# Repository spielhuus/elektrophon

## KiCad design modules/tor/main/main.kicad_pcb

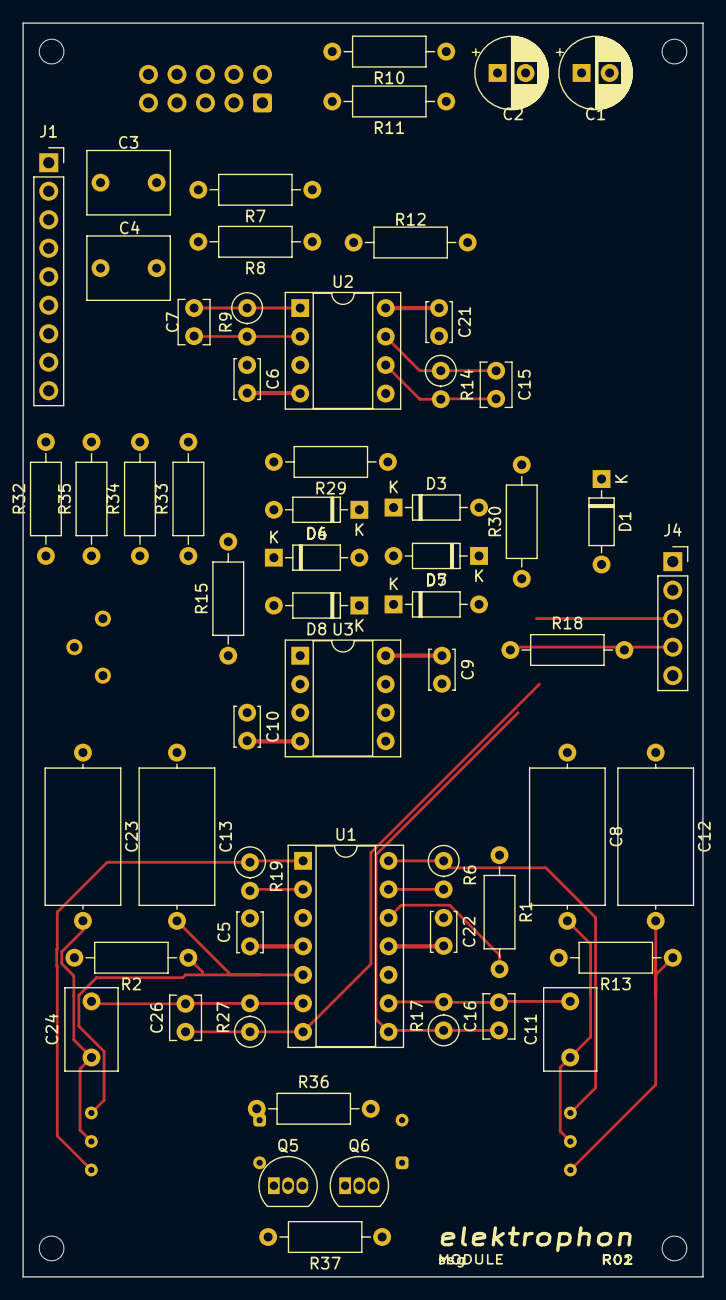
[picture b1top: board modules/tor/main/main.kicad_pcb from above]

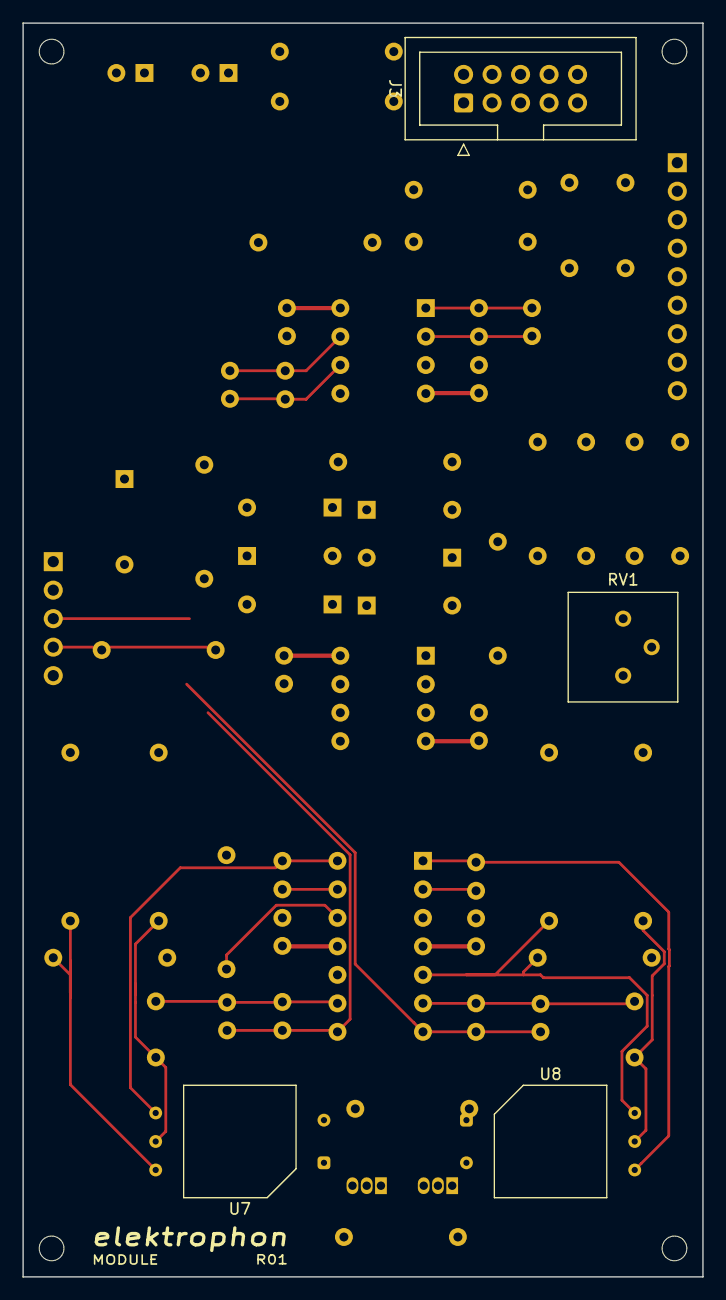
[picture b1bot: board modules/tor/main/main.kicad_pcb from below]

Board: 2 copper layers, 60.6 x 111.8 mm, 66 parts (4 on the bottom side), 44 nets.

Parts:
C1, C2: 22u; CP_Radial_D6.3mm_P2.50mm
C3, C4: 1u (NP); C_Rect_L7.2mm_W5.5mm_P5.00mm_FKS2_FKP2_MKS2_MKP2
C5, C6, C9, C10, C21, C22: 0.1u; C_Disc_D3.4mm_W2.1mm_P2.50mm
C7, C15, C16, C26: 47p; C_Disc_D3.8mm_W2.6mm_P2.50mm
C8, C23: 220p; C_Axial_L12.0mm_D6.5mm_P15.00mm_Horizontal
C11, C24: 4700p; C_Rect_L7.2mm_W4.5mm_P5.00mm_FKS2_FKP2_MKS2_MKP2
C12, C13: 1000p; C_Axial_L12.0mm_D6.5mm_P15.00mm_Horizontal
D1, D3, D4, D5, D6, D7, D8: 1N4148; D_DO-35_SOD27_P7.62mm_Horizontal
J1: Conn_01x09_Female; PinSocket_1x09_P2.54mm_Vertical
J3: IDC Header; IDC-Header_2x05_P2.54mm_Vertical
J4: Conn_01x05_Female; PinSocket_1x05_P2.54mm_Vertical
Q5: BC557; TO-92_Inline
Q6: BC547; TO-92_Inline
R1, R7, R8, R12, R15, R18, R30: 100k; R_Axial_DIN0207_L6.3mm_D2.5mm_P10.16mm_Horizontal
R2, R13: 4.7M; R_Axial_DIN0207_L6.3mm_D2.5mm_P10.16mm_Horizontal
R6, R19: 15k; R_Axial_DIN0207_L6.3mm_D2.5mm_P2.54mm_Vertical
R9, R14, R17, R27: 100k; R_Axial_DIN0207_L6.3mm_D2.5mm_P2.54mm_Vertical
R10, R11: 10; R_Axial_DIN0207_L6.3mm_D2.5mm_P10.16mm_Horizontal
R29: 10k; R_Axial_DIN0207_L6.3mm_D2.5mm_P10.16mm_Horizontal
R32, R33, R34, R35: 110k; R_Axial_DIN0207_L6.3mm_D2.5mm_P10.16mm_Horizontal
R36: 1.5k; R_Axial_DIN0207_L6.3mm_D2.5mm_P10.16mm_Horizontal
R37: 1Meg; R_Axial_DIN0207_L6.3mm_D2.5mm_P10.16mm_Horizontal
REF1, REF2, REF3, REF4: MountingHole_2.2mm_M2
RV1: 1k; Potentiometer_Bourns_3386P_Vertical
U1: TL074; DIP-14_W7.62mm_Socket
U2, U3: TL072; DIP-8_W7.62mm_Socket
U7, U8: VTL5Cx2; PerkinElmer_VTL5Cx2

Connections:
+5V: J3.9, J3.10
+15V: C1.1, C5.1, C9.1, C21.1, J1.2, R10.1, R37.1, U1.4, U2.8, U3.8, U7.2
-15V: C2.2, C6.2, C10.2, C22.2, Q5.1, R11.1, U1.11, U2.4, U3.4
/V1a: R6.1, U1.14, U7.5
/V1b: C8.2, C11.1, U7.4
/V1c: C12.2, R13.1, U1.10, U7.3
/V2a: R19.1, U1.1, U8.5
/V2b: C23.2, C24.1, U8.4
/V2c: C13.2, R2.1, U1.5, U8.3
CLIP: D1.2, J4.1
CV: J1.8, R35.2
CV2: J1.9, R32.2
FREQ: J1.7, R34.2
GND: C1.2, C2.1, C5.2, C6.1, C8.1, C9.2, C10.1, C12.1, C13.1, C21.2, C22.1, C23.1, J1.1, J3.5, J3.6, J3.7, J3.8, Q6.3, R1.1, R2.2, R13.2, R18.1, R30.1, R36.2, U2.3, U2.5
IN_1: C3.2, J1.3
IN_2: C4.2, J1.4
unnamed: C3.1, R7.2
unnamed: C4.1, R8.2
unnamed: C7.1, R9.1, R12.2, U2.1
unnamed: C7.2, R7.1, R8.1, R9.2, U2.2
unnamed: C11.2, C16.2, R17.2, U1.9
unnamed: C15.1, R1.2, R14.1, U1.12, U2.7
unnamed: C15.2, R12.1, R14.2, R15.2, U2.6
unnamed: C24.2, C26.2, R27.2, U1.6
unnamed: D1.1, D3.1, D4.2, R29.2, U3.3, U3.7
unnamed: D3.2, D5.1
unnamed: D4.1, D6.2
unnamed: D5.2, D7.1
unnamed: D6.1, D8.2
unnamed: D7.2, D8.1, R29.1, R30.2, U3.6
unnamed: Q5.2, R32.1, R33.1, R34.1, R35.1, RV1.1, RV1.2
unnamed: Q5.3, Q6.2, R37.2
unnamed: Q6.1, U8.1
unnamed: R6.2, U1.13
unnamed: R15.1, U3.1, U3.2
unnamed: R19.2, U1.2
unnamed: R36.1, RV1.3
unnamed: U7.1, U8.2
OUT_A: C16.1, J4.4, R17.1, R18.2, U1.3, U1.8
OUT_B: C26.1, J4.3, R27.1, U1.7
RES: J4.2, U3.5
VN: J3.1, J3.2, R11.2
VP: J3.3, J3.4, R10.2
V_OCT: J1.6, R33.2

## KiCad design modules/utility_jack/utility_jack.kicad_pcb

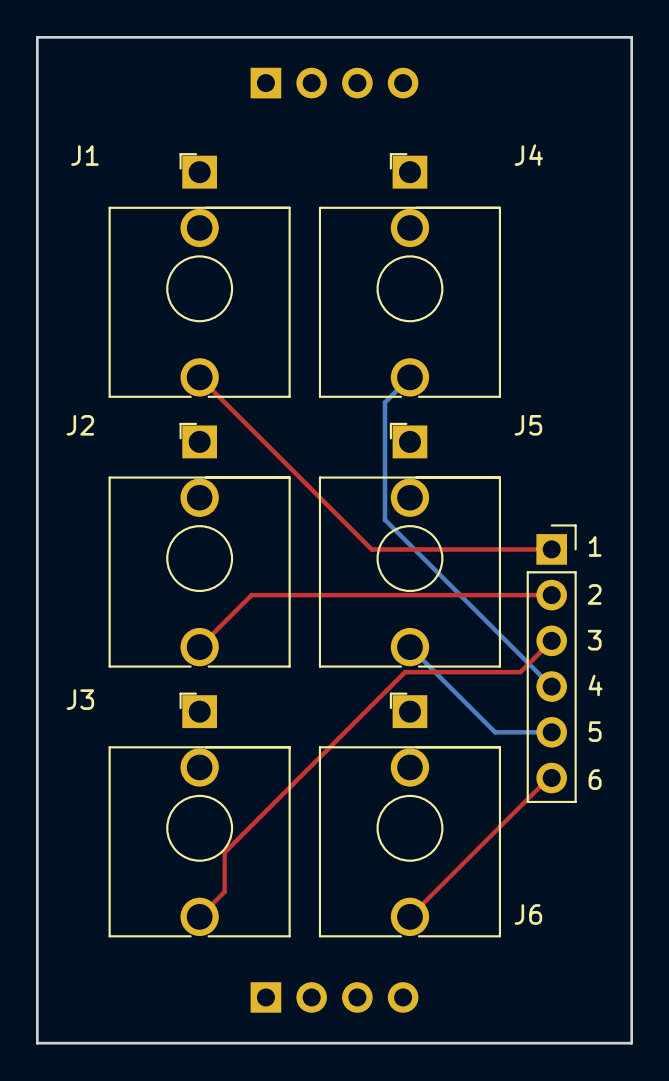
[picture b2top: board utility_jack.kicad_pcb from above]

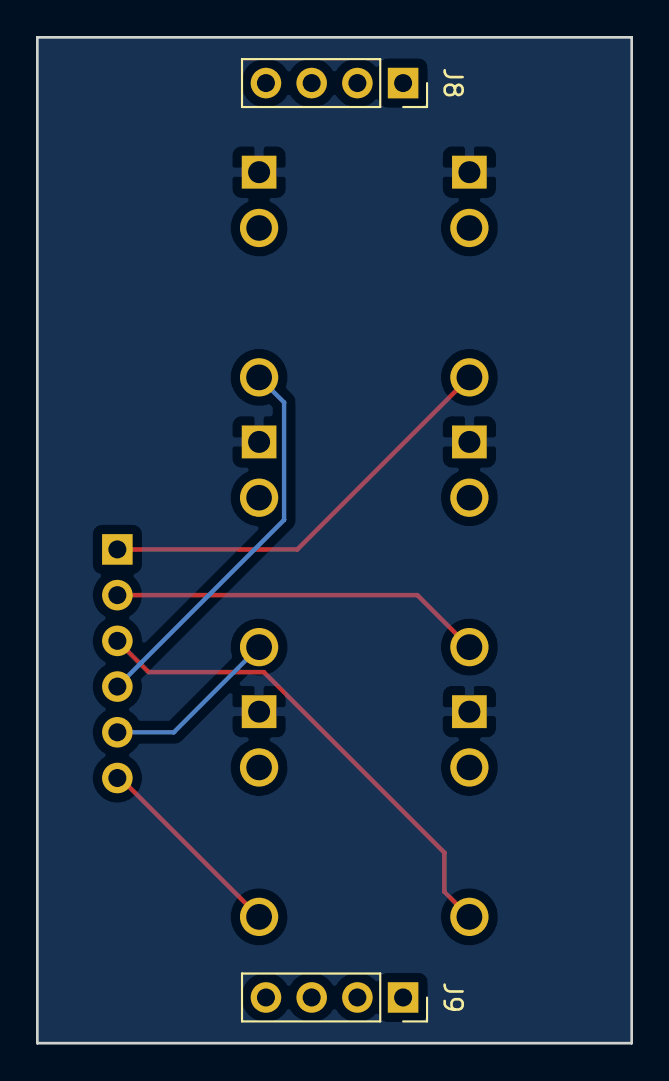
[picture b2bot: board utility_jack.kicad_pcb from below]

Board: 2 copper layers, 33.0 x 55.9 mm, 9 parts (2 on the bottom side), 7 nets.

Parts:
J1, J2, J3, J4, J5, J6: #1; Jack_3.5mm_WQP-PJ301BM_Vertical
J7: Conn_01x06_Female; PinSocket_1x06_P2.54mm_Vertical
J8, J9: Conn_01x04_Male; PinSocket_1x04_P2.54mm_Vertical

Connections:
GND: J1.S, J2.S, J3.S, J4.S, J5.S, J6.S
IN_1: J1.T, J7.1
IN_2: J2.T, J7.2
IN_3: J3.T, J7.3
IN_4: J4.T, J7.4
IN_5: J5.T, J7.5
IN_6: J6.T, J7.6

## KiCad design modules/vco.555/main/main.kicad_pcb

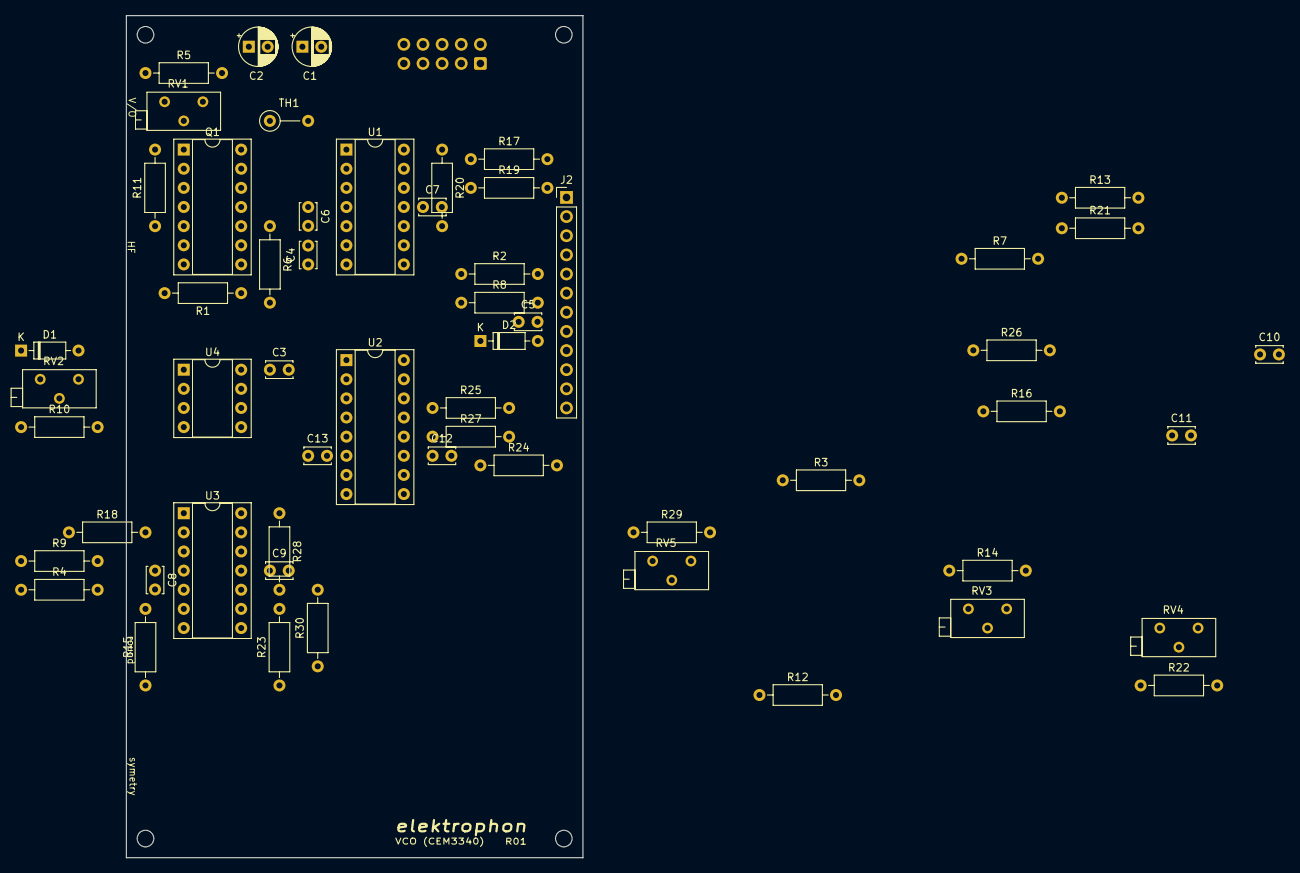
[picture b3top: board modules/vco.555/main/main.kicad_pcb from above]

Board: 2 copper layers, 60.6 x 111.8 mm, 62 parts (1 on the bottom side), 43 nets, no tracks yet.

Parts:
C1, C2: 10u; CP_Radial_D5.0mm_P2.50mm
C3, C6, C7, C8, C9, C12, C13: 0.1u; C_Disc_D3.4mm_W2.1mm_P2.50mm
C4: 100p; C_Disc_D3.4mm_W2.1mm_P2.50mm
C5: 470p; C_Disc_D3.4mm_W2.1mm_P2.50mm
C10: 2200p; C_Disc_D3.4mm_W2.1mm_P2.50mm
C11: 0.001u; C_Disc_D3.4mm_W2.1mm_P2.50mm
D1, D2: 1N4148; D_DO-35_SOD27_P7.62mm_Horizontal
H1, H2, H3, H4: MountingHole; MountingHole_2.2mm_M2
J1: IDC Header; IDC-Header_2x05_P2.54mm_Vertical
J2: Conn_01x12_Female; PinHeader_1x12_P2.54mm_Vertical
Q1: THAT340; DIP-14_W7.62mm_Socket
R1: 1M5; R_Axial_DIN0207_L6.3mm_D2.5mm_P10.16mm_Horizontal
R2, R10, R14, R22: 1M; R_Axial_DIN0207_L6.3mm_D2.5mm_P10.16mm_Horizontal
R3, R11: 4k7; R_Axial_DIN0207_L6.3mm_D2.5mm_P10.16mm_Horizontal
R4, R7: 1k5; R_Axial_DIN0207_L6.3mm_D2.5mm_P10.16mm_Horizontal
R5, R25: 390; R_Axial_DIN0207_L6.3mm_D2.5mm_P10.16mm_Horizontal
R6: 22k; R_Axial_DIN0207_L6.3mm_D2.5mm_P10.16mm_Horizontal
R8, R13, R15, R24: 100k; R_Axial_DIN0207_L6.3mm_D2.5mm_P10.16mm_Horizontal
R9, R16, R17, R18, R21: 10k; R_Axial_DIN0207_L6.3mm_D2.5mm_P10.16mm_Horizontal
R12: 150k; R_Axial_DIN0207_L6.3mm_D2.5mm_P10.16mm_Horizontal
R19, R20: 20k; R_Axial_DIN0207_L6.3mm_D2.5mm_P10.16mm_Horizontal
R23: 120k; R_Axial_DIN0207_L6.3mm_D2.5mm_P10.16mm_Horizontal
R26: 2k2; R_Axial_DIN0207_L6.3mm_D2.5mm_P10.16mm_Horizontal
R27, R29: 39k; R_Axial_DIN0207_L6.3mm_D2.5mm_P10.16mm_Horizontal
R28: 2M2; R_Axial_DIN0207_L6.3mm_D2.5mm_P10.16mm_Horizontal
R30: 300k; R_Axial_DIN0207_L6.3mm_D2.5mm_P10.16mm_Horizontal
RV1: 100; Potentiometer_Bourns_3296Z_Horizontal
RV2, RV3, RV4: 100k; Potentiometer_Bourns_3296Z_Horizontal
RV5: 25k; Potentiometer_Bourns_3296Z_Horizontal
TH1: 2k +3500ppm/°C; R_Axial_DIN0207_L6.3mm_D2.5mm_P5.08mm_Vertical
U1, U3: TL074; DIP-14_W7.62mm_Socket
U2: LM13700; DIP-16_W7.62mm_Socket
U4: TLC555xP; DIP-8_W7.62mm_Socket

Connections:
+5V: J1.9, J1.10
+15V: C1.1, C3.1, C6.1, C8.1, C12.1, J1.3, J1.4, J2.3, R9.1, R11.1, R17.2, RV3.1, RV4.1, RV5.2, RV5.3, U1.4, U2.11, U3.4, U4.8
-15V: C2.2, C7.2, C9.2, C13.2, J1.1, J1.2, J2.2, R1.2, R12.2, RV3.3, RV4.3, U1.11, U2.6, U3.11
/exp_fm: J2.4, R10.2, TH1.2, U1.2
/lin_fm: J2.5, R2.2
/net_q: R3.2, U4.3
/pulse: J2.10, R28.1, U3.14
/pwm_cv: J2.11, R23.2, U3.9
/ramp: J2.8, R21.1, U3.1
/sine: J2.9, U2.9
/sync: C5.2, J2.6
/triangle: J2.7, R20.1, R24.1, R26.1, R27.2, U1.14
GND: C1.2, C2.1, C3.2, C6.2, C7.1, C8.2, C9.1, C10.2, C11.2, C12.2, C13.1, D2.2, J1.5, J1.6, J1.7, J1.8, J2.1, Q1.3, Q1.9, R4.2, R5.2, R7.1, R19.1, R25.2, R30.2, RV2.3, U1.3, U1.5, U2.14, U3.5, U3.10, U4.1
unnamed: C4.1, D1.2, R6.2, U1.7
unnamed: C4.2, Q1.8, R1.1, R2.1, U1.6
unnamed: C5.1, R8.2
unnamed: C10.1, U1.10, U2.5
unnamed: C11.1, U4.5
unnamed: D1.1, RV2.1
unnamed: D2.1, Q1.2, R8.1
unnamed: Q1.1, R11.2, U4.4
unnamed: Q1.6, RV1.2
unnamed: Q1.7, U2.1
unnamed: Q1.5, Q1.10, R6.1
unnamed: R3.1, R7.2, U2.3
unnamed: R4.1, R9.2, U2.4
unnamed: R5.1, RV1.3
unnamed: R10.1, RV2.2
unnamed: R12.1, R13.1, R14.2, R15.2, U3.6
unnamed: R13.2, U1.8, U1.9, U1.12, U4.2, U4.6
unnamed: R14.1, RV3.2
unnamed: R15.1, R16.1, R18.1, U3.7
unnamed: R16.2, U3.3, U4.7
unnamed: R17.1, R19.2, R20.2, U1.13
unnamed: R18.2, R21.2, U3.2
unnamed: R22.1, R24.2, R25.1, U2.13
unnamed: R22.2, RV4.2
unnamed: R23.1, U3.8, U3.13
unnamed: R26.2, R28.2, U3.12
unnamed: R27.1, R30.1, U2.10, U2.12
unnamed: R29.1, U2.16
unnamed: R29.2, RV5.1
unnamed: RV1.1, TH1.1, U1.1

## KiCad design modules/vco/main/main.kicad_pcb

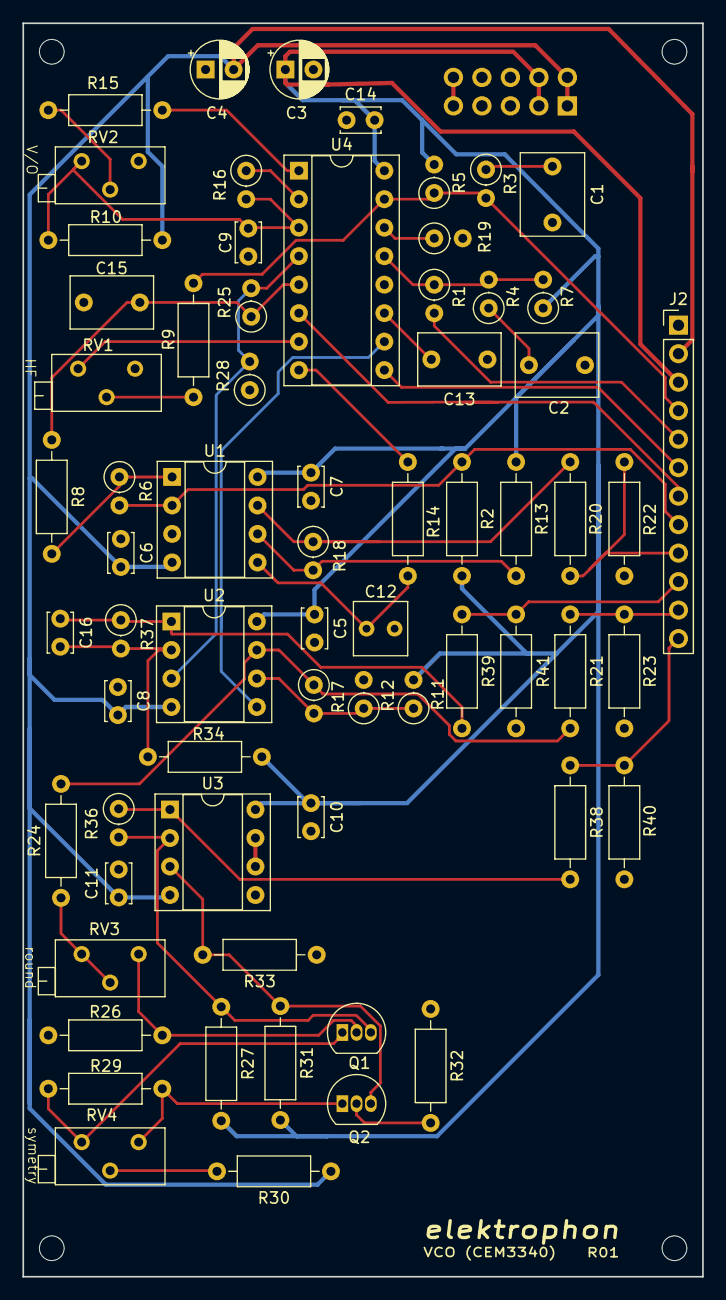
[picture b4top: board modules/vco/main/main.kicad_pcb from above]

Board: 2 copper layers, 60.6 x 111.8 mm, 72 parts (1 on the bottom side), 46 nets.

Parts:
C1, C2: 0.01u; C_Rect_L7.2mm_W5.5mm_P5.00mm_FKS2_FKP2_MKS2_MKP2
C3, C4: 10u; CP_Radial_D5.0mm_P2.50mm
C5, C6, C7, C8, C9, C10, C11, C14: 0.1u; C_Disc_D3.4mm_W2.1mm_P2.50mm
C12: 33p; C_Rect_L4.6mm_W4.6mm_P2.50mm_MKS02_FKP02
C13: 1000p; C_Rect_L7.2mm_W4.5mm_P5.00mm_FKS2_FKP2_MKS2_MKP2
C15: 0.001u; C_Rect_L7.2mm_W4.5mm_P5.00mm_FKS2_FKP2_MKS2_MKP2
C16: 22p; C_Disc_D3.4mm_W2.1mm_P2.50mm
H1, H2, H3, H4: MountingHole; MountingHole_2.2mm_M2
J1: IDC Header; IDC-Header_2x05_P2.54mm_Vertical
J2: Conn_01x12_Female; PinHeader_1x12_P2.54mm_Vertical
Q1, Q2: 2N3904; TO-92_Inline
R1, R25: 1M; R_Axial_DIN0207_L6.3mm_D2.5mm_P2.54mm_Vertical
R2: 10M; R_Axial_DIN0207_L6.3mm_D2.5mm_P10.16mm_Horizontal
R3, R4: 470; R_Axial_DIN0207_L6.3mm_D2.5mm_P2.54mm_Vertical
R5: 360k; R_Axial_DIN0207_L6.3mm_D2.5mm_P2.54mm_Vertical
R6: 120k; R_Axial_DIN0207_L6.3mm_D2.5mm_P2.54mm_Vertical
R7: 1M5; R_Axial_DIN0207_L6.3mm_D2.5mm_P2.54mm_Vertical
R8, R14, R27, R31: 10k; R_Axial_DIN0207_L6.3mm_D2.5mm_P10.16mm_Horizontal
R9: 1M; R_Axial_DIN0207_L6.3mm_D2.5mm_P10.16mm_Horizontal
R10: 820k; R_Axial_DIN0207_L6.3mm_D2.5mm_P10.16mm_Horizontal
R11: 30k; R_Axial_DIN0207_L6.3mm_D2.5mm_P2.54mm_Vertical
R12, R18, R28: 10k; R_Axial_DIN0207_L6.3mm_D2.5mm_P2.54mm_Vertical
R13, R33: 20k; R_Axial_DIN0207_L6.3mm_D2.5mm_P10.16mm_Horizontal
R15: 24k; R_Axial_DIN0207_L6.3mm_D2.5mm_P10.16mm_Horizontal
R16: 5k6; R_Axial_DIN0207_L6.3mm_D2.5mm_P2.54mm_Vertical
R17: 15k; R_Axial_DIN0207_L6.3mm_D2.5mm_P2.54mm_Vertical
R19: 1k8; R_Axial_DIN0207_L6.3mm_D2.5mm_P2.54mm_Vertical
R20, R21, R41: 1k5; R_Axial_DIN0207_L6.3mm_D2.5mm_P10.16mm_Horizontal
R22, R23: 3k; R_Axial_DIN0207_L6.3mm_D2.5mm_P10.16mm_Horizontal
R24: 47k; R_Axial_DIN0207_L6.3mm_D2.5mm_P10.16mm_Horizontal
R26, R32: 2k2; R_Axial_DIN0207_L6.3mm_D2.5mm_P10.16mm_Horizontal
R29: 390; R_Axial_DIN0207_L6.3mm_D2.5mm_P10.16mm_Horizontal
R30: 18k; R_Axial_DIN0207_L6.3mm_D2.5mm_P10.16mm_Horizontal
R34: 40k; R_Axial_DIN0207_L6.3mm_D2.5mm_P10.16mm_Horizontal
R36: 20k; R_Axial_DIN0207_L6.3mm_D2.5mm_P2.54mm_Vertical
R37: 33k; R_Axial_DIN0207_L6.3mm_D2.5mm_P2.54mm_Vertical
R38, R40: 2k; R_Axial_DIN0207_L6.3mm_D2.5mm_P10.16mm_Horizontal
R39: 2k26; R_Axial_DIN0207_L6.3mm_D2.5mm_P10.16mm_Horizontal
RV1, RV2: 10k; Potentiometer_Bourns_3296Z_Horizontal
RV3, RV4: 50k; Potentiometer_Bourns_3296Z_Horizontal
U1, U2, U3: TL072; DIP-8_W7.62mm_Socket
U4: CEM3340; DIP-16_W7.62mm_Socket

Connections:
+5V: J1.9, J1.10
+15V: C3.1, C5.1, C7.1, C10.1, C14.2, J1.3, J1.4, J2.3, R2.1, R5.2, R7.1, R11.2, R13.2, R27.2, R31.2, R34.2, U1.8, U2.8, U3.8, U4.16
-15V: C4.2, C6.2, C8.2, C11.2, J1.1, J1.2, J2.2, R10.2, R30.1, U1.4, U2.4, U3.4
/CV: J2.4, R3.2, R5.1, R9.1, U4.15
/HARD_SYNC: J2.7, U4.6
/HF_Trim: RV1.3, U4.7
/IN_LIN_FM: J2.5, R1.2
/IN_PWM: J2.8, R2.2, R6.2, U1.2
/LIN_FM: R1.1, R4.2, R7.2, U4.13
/PULSE: J2.10, R39.1, R41.2
/PULSE_RAW: R25.2, R28.2, U2.3, U4.4
/PWM: C15.2, R8.1, R25.1, U4.5
/SAW: J2.9, R20.1, R22.2
/SAW_RAW: R14.2, U4.8
/SINE: J2.12, R38.1, R40.2
/SOFT_SYNC: J2.6, U4.9
/TRIANGLE: J2.11, R21.1, R23.2
/TRI_RAW: U2.5, U4.10
GND: C1.2, C2.2, C3.2, C4.1, C5.2, C6.1, C7.2, C8.1, C9.2, C10.2, C11.1, C12.2, C13.2, C14.1, C15.1, J1.5, J1.6, J1.7, J1.8, J2.1, R12.2, R19.2, R22.1, R23.1, R26.1, R28.1, R32.1, R33.1, R40.1, R41.1, RV1.1, U1.3, U3.5, U4.12
unnamed: C1.1, R3.1
unnamed: C2.1, R4.1
unnamed: C9.1, R10.1, R16.2, RV2.3, U4.3
unnamed: C12.1, R14.1, U1.5
unnamed: C13.1, U4.11
unnamed: C16.1, R37.1, R39.2, U2.1
unnamed: C16.2, R34.1, R37.2, U2.2
unnamed: Q1.1, R29.2, RV4.3
unnamed: Q1.2, R26.2, RV3.1
unnamed: Q1.3, R27.1, R36.2, U3.2
unnamed: Q2.1, R29.1, RV4.1
unnamed: Q2.2, R32.2
unnamed: Q2.3, R31.1, R33.2, U3.3
unnamed: R6.1, R8.2, U1.1
unnamed: R9.2, RV1.2
unnamed: R11.1, R12.1, R17.2, U2.6
unnamed: R13.1, R18.2, U1.6
unnamed: R15.1, U4.1
unnamed: R15.2, RV2.2
unnamed: R16.1, U4.2
unnamed: R17.1, R21.2, R24.2, U2.7
unnamed: R18.1, R20.2, U1.7
unnamed: R19.1, U4.14
unnamed: R24.1, RV3.2, RV3.3
unnamed: R30.2, RV4.2
unnamed: R36.1, R38.2, U3.1
unnamed: U3.6, U3.7

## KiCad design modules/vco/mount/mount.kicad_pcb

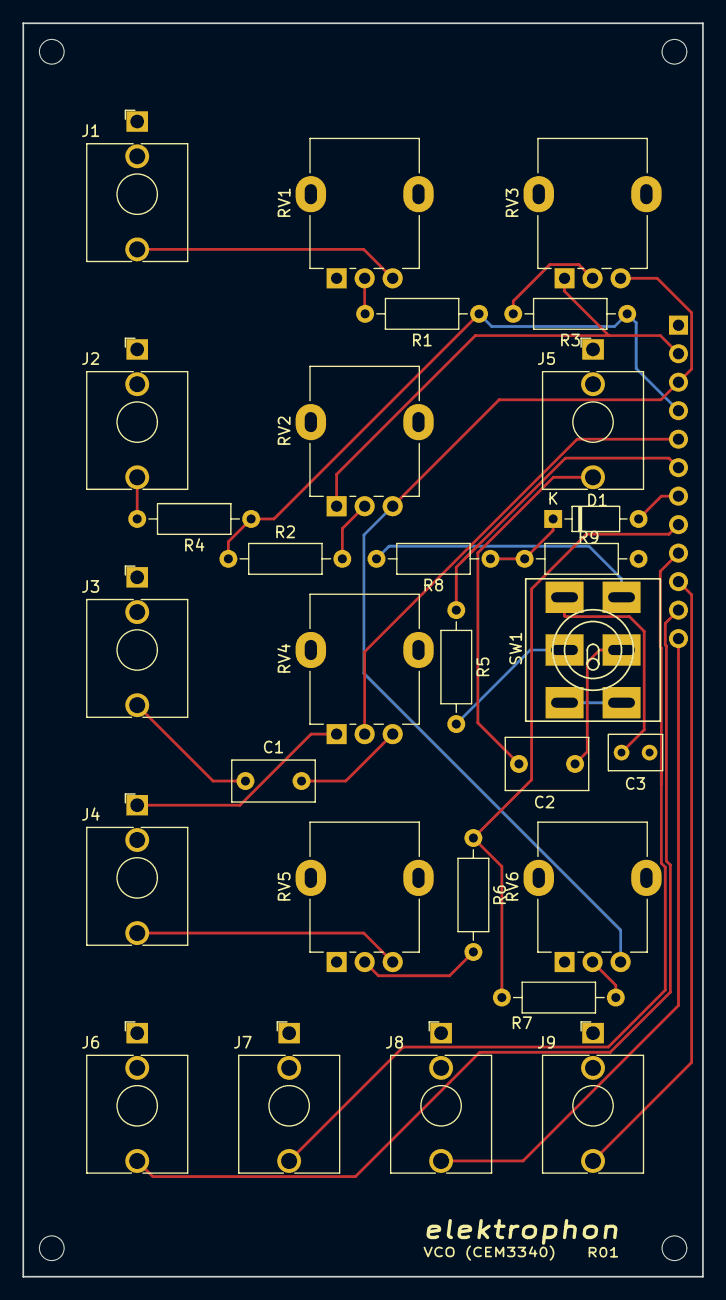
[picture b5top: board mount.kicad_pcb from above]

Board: 2 copper layers, 60.6 x 111.8 mm, 34 parts (1 on the bottom side), 29 nets.

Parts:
C1: 0.22u; C_Rect_L7.2mm_W3.5mm_P5.00mm_FKS2_FKP2_MKS2_MKP2
C2: 0.001u; C_Rect_L7.2mm_W4.5mm_P5.00mm_FKS2_FKP2_MKS2_MKP2
C3: 0.1u; C_Rect_L4.6mm_W3.0mm_P2.50mm_MKS02_FKP02
D1: 1N4148; D_DO-35_SOD27_P7.62mm_Horizontal
H1, H2, H3, H4: MountingHole; MountingHole_2.2mm_M2
J1, J2, J3, J4, J5, J6, J7, J8, J9: AudioJack2_SwitchT; Jack_3.5mm_WQP-PJ398SM_Vertical
J10: Conn_01x12_Male; PinHeader_1x12_P2.54mm_Vertical
R1, R2, R4, R6: 100k; R_Axial_DIN0207_L6.3mm_D2.5mm_P10.16mm_Horizontal
R3: 3M3; R_Axial_DIN0207_L6.3mm_D2.5mm_P10.16mm_Horizontal
R5: 47k; R_Axial_DIN0207_L6.3mm_D2.5mm_P10.16mm_Horizontal
R7: 300k; R_Axial_DIN0207_L6.3mm_D2.5mm_P10.16mm_Horizontal
R8: 5k6; R_Axial_DIN0207_L6.3mm_D2.5mm_P10.16mm_Horizontal
R9: 10k; R_Axial_DIN0207_L6.3mm_D2.5mm_P10.16mm_Horizontal
RV1, RV2, RV3, RV4, RV5, RV6: 100k; Potentiometer_Alpha_RD901F-40-00D_Single_Vertical
SW1: SW_DPDT_x2; Tumbler_SW_x2

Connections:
+15V: J10.3, RV2.3, RV3.3, RV6.3
-15V: J10.2, RV2.1, RV3.1
/CV: J10.4, R1.1, R2.1, R3.1, R4.1
/HARD_SYNC: D1.2, J10.7
/IN_LIN_FM: J10.5, RV4.2
/IN_PWM: J10.8, R6.1, R7.1
/PULSE: J9.T, J10.10
/SAW: J7.T, J10.9
/SINE: J8.T, J10.12
/SOFT_SYNC: J10.6, R5.2
/TRIANGLE: J6.T, J10.11
GND: C3.2, J1.S, J2.S, J3.S, J4.S, J5.S, J5.TN, J6.S, J7.S, J8.S, J9.S, J10.1, R9.1, RV1.1, RV4.1, RV5.1, RV6.1
unnamed: C1.1, J3.T
unnamed: C1.2, RV4.3
unnamed: C2.1, J5.T
unnamed: C2.2, SW1.2
unnamed: C3.1, SW1.6
unnamed: D1.1, R8.1, R9.2
unnamed: J1.T, RV1.3
unnamed: J2.T, R4.2
unnamed: J4.T, RV5.3
unnamed: R1.2, RV1.2
unnamed: R2.2, RV2.2
unnamed: R3.2, RV3.2
unnamed: R5.1, SW1.5
unnamed: R6.2, RV5.2
unnamed: R7.2, RV6.2
unnamed: R8.2, SW1.3
unnamed: SW1.1, SW1.4

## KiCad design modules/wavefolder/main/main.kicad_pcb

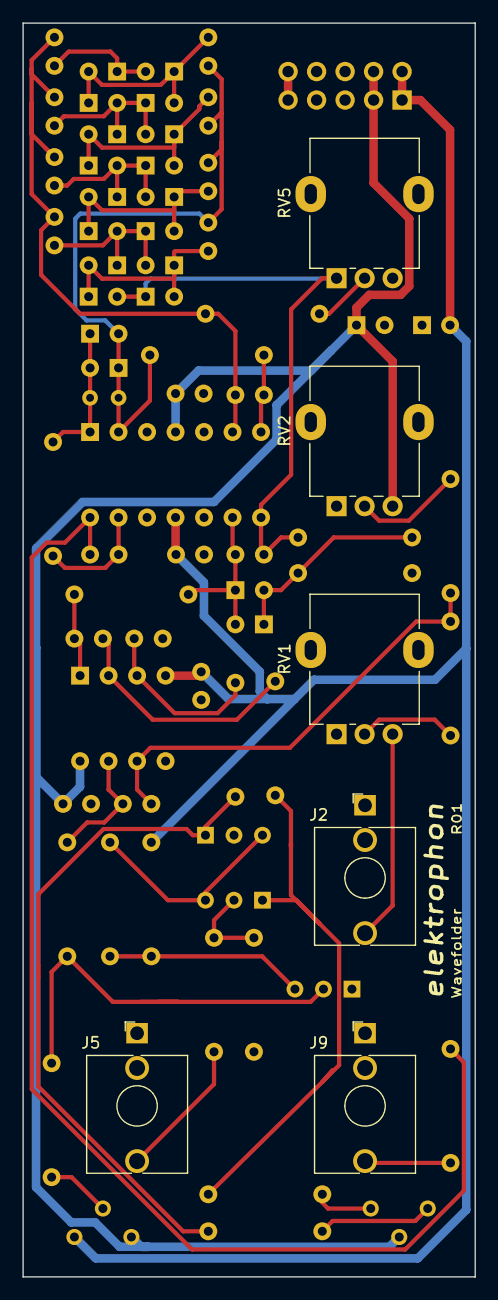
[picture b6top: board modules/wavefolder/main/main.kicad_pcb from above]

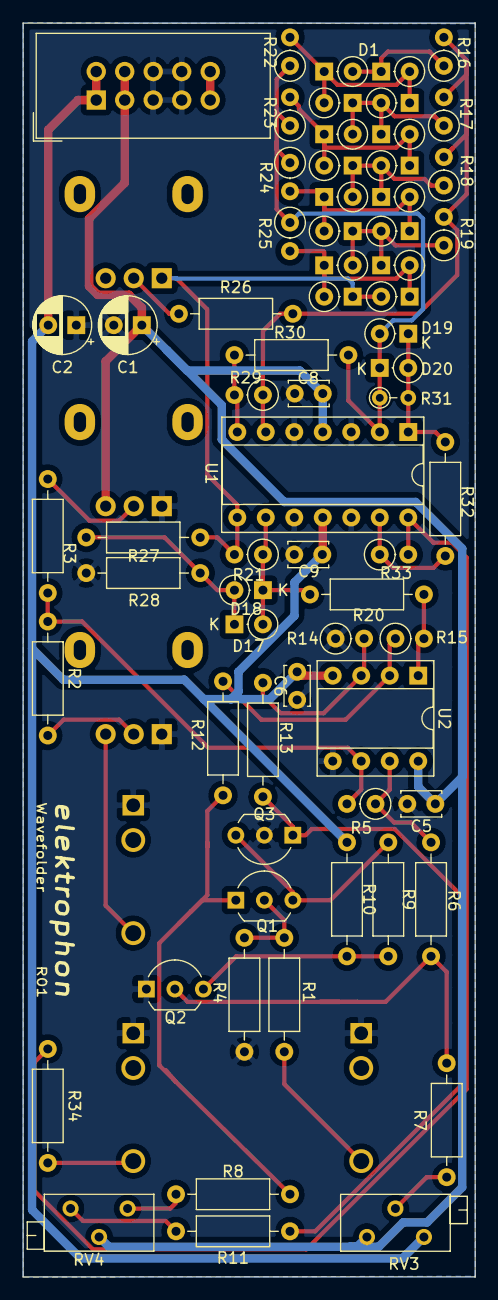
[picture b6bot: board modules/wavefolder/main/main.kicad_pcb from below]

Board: 2 copper layers, 40.3 x 111.8 mm, 74 parts (68 on the bottom side), 41 nets.

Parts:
C1, C2: 10u; CP_Radial_D5.0mm_P2.50mm
C5, C6, C8, C9: 0.1u; C_Disc_D3.4mm_W2.1mm_P2.50mm
D1, D2, D3, D4, D5, D6, D7, D8, D9, D10, D11, D12, D13, D14, D15, D16, D17, D18, D19, D20: D; D_DO-35_SOD27_P2.54mm_Vertical_KathodeUp
J2: Control; Jack_3.5mm_WQP-PJ398SM_Vertical
J5: INPUT; Jack_3.5mm_WQP-PJ398SM_Vertical
J6: POWER; IDC-Header_2x05_P2.54mm_Vertical
J9: OUT; Jack_3.5mm_WQP-PJ398SM_Vertical
Q1, Q2, Q3: BC547; TO-92_Inline_Wide
R1, R3, R20: 100k; R_Axial_DIN0207_L6.3mm_D2.5mm_P10.16mm_Horizontal
R2: 68k; R_Axial_DIN0207_L6.3mm_D2.5mm_P10.16mm_Horizontal
R4: 680; R_Axial_DIN0207_L6.3mm_D2.5mm_P10.16mm_Horizontal
R5, R14, R15, R21: 100k; R_Axial_DIN0207_L6.3mm_D2.5mm_P2.54mm_Vertical
R6, R7: 22k; R_Axial_DIN0207_L6.3mm_D2.5mm_P10.16mm_Horizontal
R8, R10, R11: 15k; R_Axial_DIN0207_L6.3mm_D2.5mm_P10.16mm_Horizontal
R9, R27: 33k; R_Axial_DIN0207_L6.3mm_D2.5mm_P10.16mm_Horizontal
R12, R13: 10k; R_Axial_DIN0207_L6.3mm_D2.5mm_P10.16mm_Horizontal
R16, R17, R18, R19, R22, R23, R24, R25: 15k; R_Axial_DIN0207_L6.3mm_D2.5mm_P2.54mm_Vertical
R26: 27k; R_Axial_DIN0207_L6.3mm_D2.5mm_P10.16mm_Horizontal
R28: 2k7; R_Axial_DIN0207_L6.3mm_D2.5mm_P10.16mm_Horizontal
R29: 5k6; R_Axial_DIN0207_L6.3mm_D2.5mm_P2.54mm_Vertical
R30: 5k6; R_Axial_DIN0207_L6.3mm_D2.5mm_P10.16mm_Horizontal
R31: 56k; R_Axial_DIN0204_L3.6mm_D1.6mm_P2.54mm_Vertical
R32: 6k8; R_Axial_DIN0207_L6.3mm_D2.5mm_P10.16mm_Horizontal
R33: 56k; R_Axial_DIN0207_L6.3mm_D2.5mm_P2.54mm_Vertical
R34: 470; R_Axial_DIN0207_L6.3mm_D2.5mm_P10.16mm_Horizontal
RV1, RV2: 100k; Potentiometer_Alpha_RD901F-40-00D_Single_Vertical
RV3: 50k; Potentiometer_Bourns_3296Z_Horizontal
RV4: 1k; Potentiometer_Bourns_3296Z_Horizontal
RV5: 47k; Potentiometer_Alpha_RD901F-40-00D_Single_Vertical
U1: TL074; DIP-14_W7.62mm_Socket
U2: TL072; DIP-8_W7.62mm_Socket

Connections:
+5V: J6.9, J6.10
+15V: C1.1, C5.1, C8.1, J6.3, J6.4, RV2.3, RV3.1, RV4.2, U1.4, U2.8
-15V: C2.2, C6.2, C9.2, J6.1, J6.2, R10.1, RV3.3, U1.11, U2.4
GND: C1.2, C2.1, C5.2, C6.1, C8.2, C9.1, J2.S, J5.S, J6.5, J6.6, J6.7, J6.8, J9.S, Q2.1, Q3.2, R4.1, R14.1, R28.1, RV1.1, RV2.1, U1.3, U1.5, U1.10, U1.12, U2.5
unnamed: D1.1, D9.2, R16.1
unnamed: D1.2, D2.1, D9.1, D10.2, R22.2
unnamed: D2.2, D3.1, D10.1, D11.2, R17.1
unnamed: D3.2, D4.1, D11.1, D12.2, R23.2
unnamed: D4.2, D5.1, D12.1, D13.2, R18.1
unnamed: D5.2, D6.1, D13.1, D14.2, R24.2
unnamed: D6.2, D7.1, D14.1, D15.2, R19.1
unnamed: D7.2, D8.1, D15.1, D16.2, R25.2
unnamed: D8.2, D16.1, R21.2, R27.1, RV5.1, U1.8
unnamed: D17.1, D18.2, R27.2, R28.2
unnamed: D17.2, D18.1, R20.2, R21.1, U1.9
unnamed: D19.1, D20.2, R31.2, R32.1, U1.1
unnamed: D19.2, D20.1, R22.1, R23.1, R24.1, R25.1, R30.2, R31.1, U1.2
unnamed: J2.T, RV1.3
unnamed: J5.T, R1.2
unnamed: J9.T, R34.2
unnamed: Q1.1, R8.1, R12.2
unnamed: Q1.2, R1.1, R4.2
unnamed: Q1.3, Q3.3, R9.2
unnamed: Q2.2, R6.1, R7.2
unnamed: Q2.3, R9.1, R10.2
unnamed: Q3.1, R11.1, R13.2
unnamed: R2.1, R3.1, R5.2, U2.6
unnamed: R2.2, RV1.2
unnamed: R3.2, RV2.2
unnamed: R5.1, R6.2, U2.7
unnamed: R7.1, RV3.2
unnamed: R8.2, RV4.1
unnamed: R11.2, RV4.3
unnamed: R12.1, R15.1, U2.2
unnamed: R13.1, R14.2, U2.3
unnamed: R15.2, R20.1, U2.1
unnamed: R16.2, R17.2, R18.2, R19.2, R26.2, R29.1, U1.6
unnamed: R26.1, RV5.2
unnamed: R29.2, R30.1, U1.7
unnamed: R32.2, R33.1, U1.13
unnamed: R33.2, R34.1, U1.14

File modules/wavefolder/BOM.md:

## BOM: Wavefolder

### main panel

|Qty|Reference(s)                                                                             |Value  |Footprint                                                     |
|---|-----------------------------------------------------------------------------------------|-------|--------------------------------------------------------------|
|2  |C1, C2                                                                                   |10u    |Capacitor_THT:CP_Radial_D5.0mm_P2.50mm                        |
|4  |C5, C6, C8, C9                                                                           |0.1u   |Capacitor_THT:C_Disc_D3.4mm_W2.1mm_P2.50mm                    |
|20 |D1, D2, D3, D4, D5, D6, D7, D8, D9, D10, D11, D12, D13, D14, D15, D16, D17, D18, D19, D20|D      |Diode_THT:D_DO-35_SOD27_P2.54mm_Vertical_KathodeUp            |
|1  |J2                                                                                       |Control|elektrophon:Jack_3.5mm_WQP-PJ398SM_Vertical                   |
|1  |J5                                                                                       |INPUT  |elektrophon:Jack_3.5mm_WQP-PJ398SM_Vertical                   |
|1  |J6                                                                                       |POWER  |Connector_IDC:IDC-Header_2x05_P2.54mm_Vertical                |
|1  |J9                                                                                       |OUT    |elektrophon:Jack_3.5mm_WQP-PJ398SM_Vertical                   |
|3  |Q1, Q2, Q3                                                                               |BC547  |Package_TO_SOT_THT:TO-92_Inline                               |
|3  |R1, R3, R20                                                                              |100k   |Resistor_THT:R_Axial_DIN0207_L6.3mm_D2.5mm_P10.16mm_Horizontal|
|1  |R2                                                                                       |68k    |Resistor_THT:R_Axial_DIN0207_L6.3mm_D2.5mm_P10.16mm_Horizontal|
|1  |R4                                                                                       |680    |Resistor_THT:R_Axial_DIN0207_L6.3mm_D2.5mm_P10.16mm_Horizontal|
|4  |R5, R14, R15, R21                                                                        |100k   |Resistor_THT:R_Axial_DIN0207_L6.3mm_D2.5mm_P2.54mm_Vertical   |
|2  |R6, R7                                                                                   |22k    |Resistor_THT:R_Axial_DIN0207_L6.3mm_D2.5mm_P10.16mm_Horizontal|
|3  |R8, R10, R11                                                                             |15k    |Resistor_THT:R_Axial_DIN0207_L6.3mm_D2.5mm_P10.16mm_Horizontal|
|2  |R9, R27                                                                                  |33k    |Resistor_THT:R_Axial_DIN0207_L6.3mm_D2.5mm_P10.16mm_Horizontal|
|2  |R12, R13                                                                                 |10k    |Resistor_THT:R_Axial_DIN0207_L6.3mm_D2.5mm_P10.16mm_Horizontal|
|8  |R16, R17, R18, R19, R22, R23, R24, R25                                                   |15k    |Resistor_THT:R_Axial_DIN0207_L6.3mm_D2.5mm_P2.54mm_Vertical   |
|1  |R26                                                                                      |27k    |Resistor_THT:R_Axial_DIN0207_L6.3mm_D2.5mm_P10.16mm_Horizontal|
|1  |R28                                                                                      |2k7    |Resistor_THT:R_Axial_DIN0207_L6.3mm_D2.5mm_P10.16mm_Horizontal|
|1  |R29                                                                                      |5k6    |Resistor_THT:R_Axial_DIN0207_L6.3mm_D2.5mm_P2.54mm_Vertical   |
|1  |R30                                                                                      |5k6    |Resistor_THT:R_Axial_DIN0207_L6.3mm_D2.5mm_P10.16mm_Horizontal|
|1  |R31                                                                                      |56k    |Resistor_THT:R_Axial_DIN0204_L3.6mm_D1.6mm_P2.54mm_Vertical   |
|1  |R32                                                                                      |6k8    |Resistor_THT:R_Axial_DIN0207_L6.3mm_D2.5mm_P10.16mm_Horizontal|
|1  |R33                                                                                      |56k    |Resistor_THT:R_Axial_DIN0207_L6.3mm_D2.5mm_P2.54mm_Vertical   |
|1  |R34                                                                                      |470    |Resistor_THT:R_Axial_DIN0207_L6.3mm_D2.5mm_P10.16mm_Horizontal|
|2  |RV1, RV2                                                                                 |100k   |elektrophon:Potentiometer_Alpha_RD901F-40-00D_Single_Vertical |
|1  |RV3                                                                                      |50k    |Potentiometer_THT:Potentiometer_Bourns_3296Z_Horizontal       |
|1  |RV4                                                                                      |1k     |Potentiometer_THT:Potentiometer_Bourns_3296Z_Horizontal       |
|1  |RV5                                                                                      |47k    |elektrophon:Potentiometer_Alpha_RD901F-40-00D_Single_Vertical |
|1  |U1                                                                                       |TL074  |Package_DIP:DIP-14_W7.62mm_Socket                             |
|1  |U2                                                                                       |TL072  |Package_DIP:DIP-8_W7.62mm_Socket                              |

### misc material

| Qty | Reference(s)             | Value              | Description | 
|-----|--------------------------|--------------------|-------------|
| 6   |                        | 6.35mm              | Potentiometer Knobs, colors of your choice   |

---
[![CC BY-SA](https://licensebuttons.net/l/by-sa/3.0/88x31.png)](https://c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

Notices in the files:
modules/tor/main/main.kicad_pcb:
License CC BY 4.0 - Attribution 4.0 International
modules/wavefolder/BOM.md:
[CC BY-SA](https://licensebuttons.net/l/by-sa/3.0/88x31.png)](https://creativecommons.org/licenses/by-sa/4.0/)
